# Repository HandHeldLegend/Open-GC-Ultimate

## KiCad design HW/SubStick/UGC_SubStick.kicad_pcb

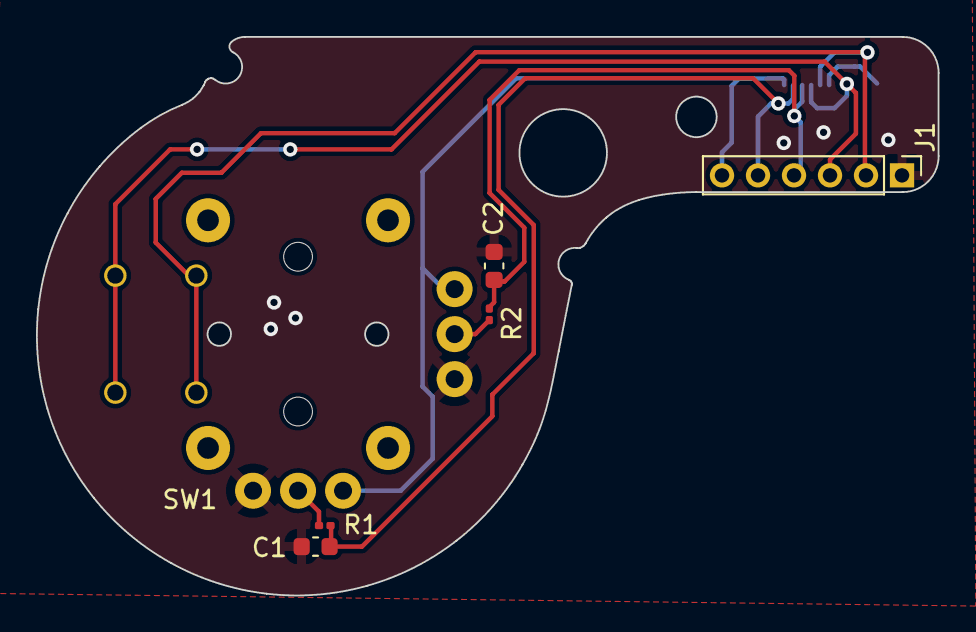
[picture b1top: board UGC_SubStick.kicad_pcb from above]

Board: 2 copper layers, 50.1 x 31.0 mm, 7 parts (1 on the bottom side), 8 nets.

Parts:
C1, C2: 47nF; C_0603_1608Metric
J1: Conn_01x06_Pin; PinHeader_1x06_P2.00mm_Vertical
J2: 503480-0640; 5034800640
R1, R2: 1k; R_0201_0603Metric
SW1: GL18_SW; GL1807SYAE

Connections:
+3V3: J1.6, J2.6, SW1.X3 (VCC), SW1.Y3 (VCC)
GND: C1.1, C2.1, J1.1, J2.1, J2.MP1, J2.MP2, SW1.X1 (GND), SW1.Y1 (GND)
unnamed: R1.1, SW1.X2 (X_OUT)
unnamed: R2.1, SW1.Y2 (Y_OUT)
RS_B_IN: J1.3, J2.3, SW1.S3 (3), SW1.S4 (4)
RS_B_OUT: J1.2, J2.2, SW1.S1 (1), SW1.S2 (2)
RX: C1.2, J1.5, J2.5, R1.2
RY: C2.2, J1.4, J2.4, R2.2

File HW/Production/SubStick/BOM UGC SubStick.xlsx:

NO | Designator | Quantity | Part Number（MPN) | Description | Value | Package | LCSC | Comment or Link | DNP
1.0 | SW1 | 1.0 | GL1807SYAE-002 | TMR Analog Stick with button | GL18_SW | - | - | -
2.0 | R1,R2 | 2.0 | RC0201FR-071KL | 50mW Thick Film Resistors 25V ±1% ±200ppm/℃ 1kΩ | 1k | 201.0 | C138165 | https://www.lcsc.com/product-detail/Chip-Resistor-Surface-Mo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
3.0 | C1,C2 | 2.0 | CC0603JRX7R9BB473 | 50V 47nF X7R ±5% | 47nF | 603.0 | C519554 | https://www.lcsc.com/product-detail/Multilayer-Ceramic-Capac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
4.0 | J2 | 1.0 | 5.03480064E9 | Connector FFC/FPC Connector Socket 6 Position 0.5mm Solder Right Angle Surface 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 | 503480-0640 | SMD,P=0.5mm,Surface Mount，Right Angle | C3168077 | https://www.lcsc.com/product-detail/FFC-FPC-Flat-Flexible-Co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

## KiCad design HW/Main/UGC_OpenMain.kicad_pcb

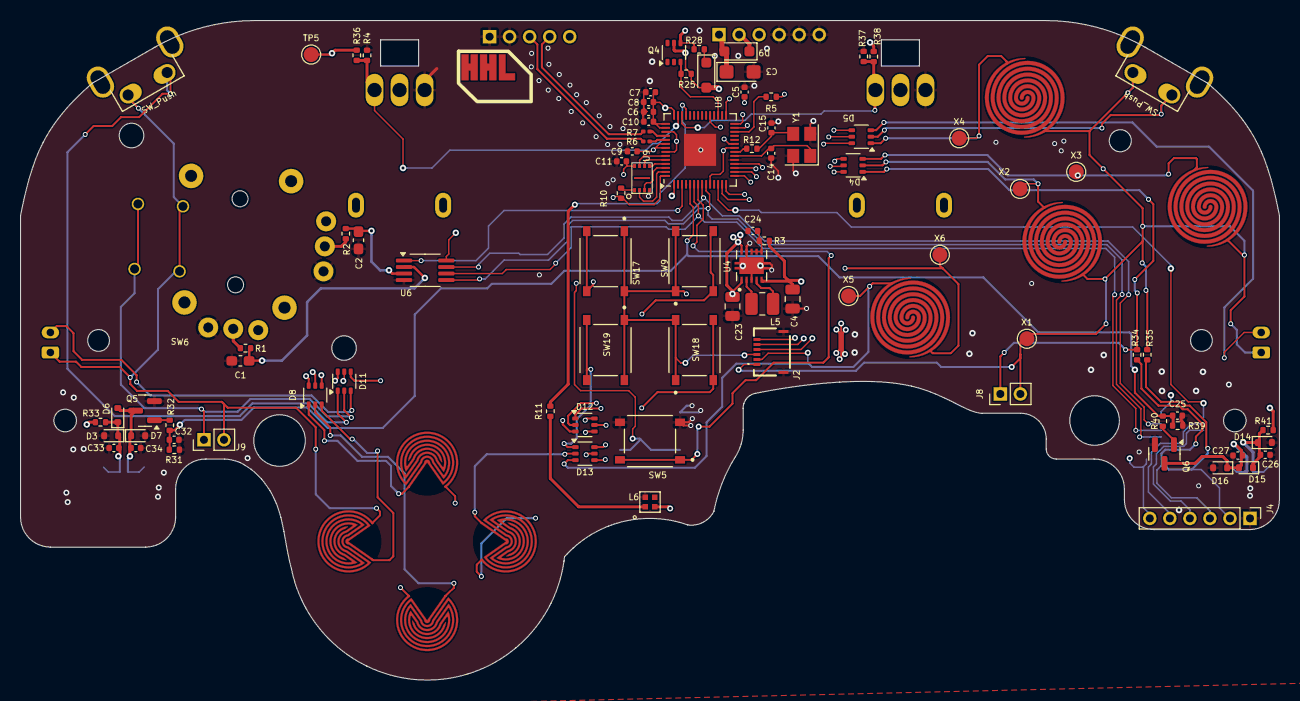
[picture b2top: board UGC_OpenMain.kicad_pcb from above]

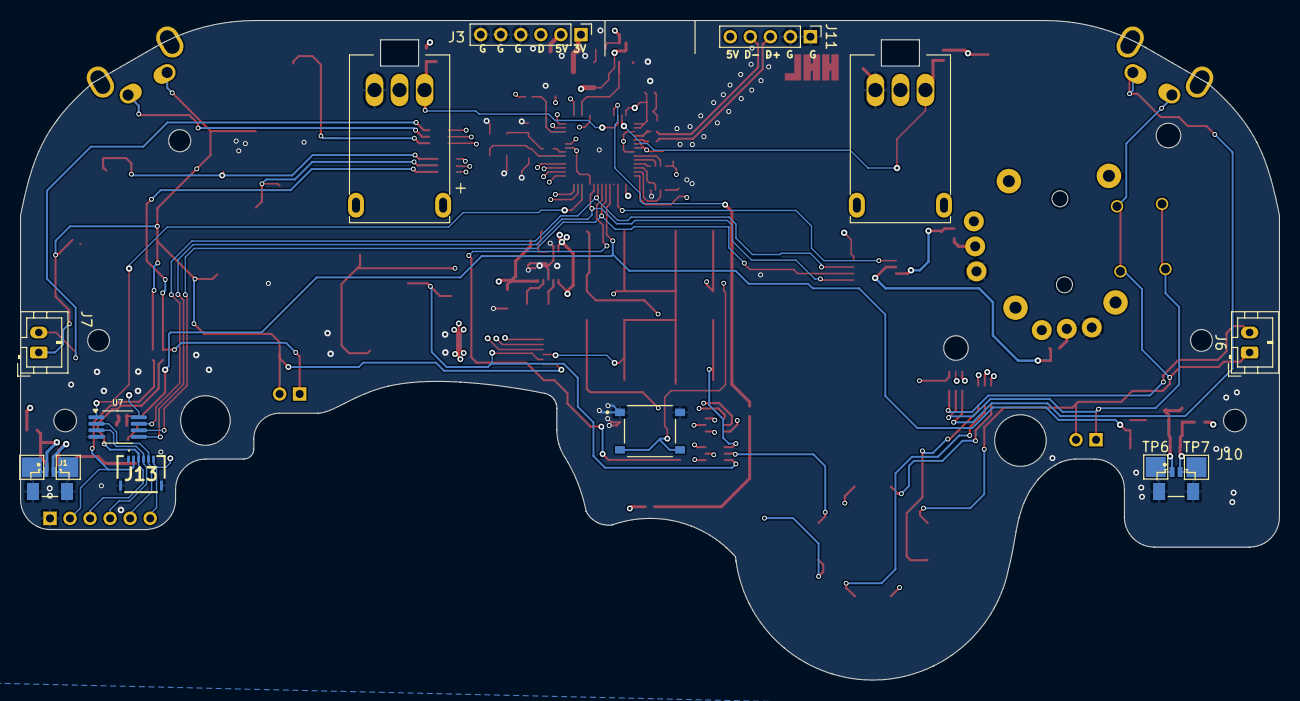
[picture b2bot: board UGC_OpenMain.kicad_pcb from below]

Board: 4 copper layers, 125.7 x 65.8 mm, 116 parts (21 on the bottom side), 78 nets.

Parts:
C1, C2: 47nF; C_0603_1608Metric_Pad1.08x0.95mm_HandSolder
C3: 47uF; CP_EIA-3216-18_Kemet-A
C4, C23: 10uF; C_0805_2012Metric
C5, C6, C7, C9, C10, C11, C24, C25, C32: 100nF; C_0402_1005Metric
C8, C26, C27, C33, C34: 1uF; C_0402_1005Metric
C14, C15: 15pF; C_0402_1005Metric
D3, D6, D7, D14, D15, D16: M7C; D_SOD-523
D4, D5, D8, D11, D12, D13: BAS16VY,115; SOT-363_SC-70-6
D9, D10: CUS08F30; D_SOD-323_HandSoldering
J1, J10: SM02B-SURS-TF_LF__SN_; JST_SM02B-SURS-TF_LF__SN_
J2, J13: 503480-0640; 5034800640
J3, J4: Conn_01x06_Pin; PinHeader_1x06_P2.00mm_Vertical
J6, J7: Trigger; JST_PH_B2B-PH-K_1x02_P2.00mm_Vertical
J8, J9: Conn_01x02; PinHeader_1x02_P2.00mm_Vertical
J11: Conn_01x05_Pin; PinHeader_1x05_P2.00mm_Vertical
L5: 1.3A 2.2uH ±20% 80mΩ; L_1008_2520Metric
L6: SK6805-EC-15
Q4: BSS138DW; SOT-363_SC-70-6
Q5, Q6: MMBT2222A; SOT-23
R1, R2, R10, R12, R25, R28: 1k; R_0402_1005Metric
R3, R32, R40: 100R; R_0402_1005Metric
R4, R36, R37, R38: 75k; R_0402_1005Metric
R5, R31, R39: 10k; R_0402_1005Metric
R6, R7: 27R; R_0201_0603Metric
R11: 330R; R_0402_1005Metric
R33, R34, R35, R41: 0R; R_0402_1005Metric
RV1, RV2: Slider_GCC-Gamecube_MB; GCC_Slider_MillMaxSocketed
S1, S2, S3, S4, S5, S6: 4015-0-43-80-30-27-10-0
SW1, SW2, SW3, SW4: SW_Push; ring_pad
SW5, SW9, SW14, SW17, SW18, SW19: SW_TS-1187A; TS-1187A-C-E-B
SW6: GL18_SW; GL1807SYAE
SW7, SW8: SW_Push; Z_Switch_Edge_Omron
SW10, SW11, SW12, SW13: SW_Push; ring_dpad
TP1, TP2, TP6, TP7: TestPoint; TestPoint_Pad_2.0x2.0mm
TP5: TestPoint; TestPoint_Pad_D1.5mm
U4: TPS630001RCR; VREG_V62_16624-01YE
U6, U7: MCP3002; MSOP-8_3x3mm_P0.65mm
U8: RP2040; QFN-56-1EP_7x7mm_P0.4mm_EP3.2x3.2mm
U9: GD25Q80EEIGR; USON-8-EP(2x3)
X1, X2, X3, X4, X5, X6: ModConnect; TestPoint_Pad_D1.5mm
Y1: ABM8-272-T3; Crystal_SMD_3225-4Pin_3.2x2.5mm

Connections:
+1V1: C5.2, U8.23 (DVDD), U8.45 (VREG_VOUT), U8.50 (DVDD)
+3V3: C6.1, C7.1, C8.1, C9.2, C10.2, C11.1, C23.1, D10.2 (A), J4.6, J13.6, L6.2 (VDD), Q4.5 (G2), R5.1, R25.1, R33.2, R36.2, R38.2, R41.2, S1.1, S4.1, SW6.X3 (VCC), SW6.Y3 (VCC), TP5.1, U4.1 (VOUT), U4.10 (FB), U6.8 (VDD/VREF), U7.8 (VDD/VREF), U8.1 (IOVDD), U8.10 (IOVDD), U8.22 (IOVDD), U8.33 (IOVDD), U8.42 (IOVDD), U8.43 (ADC_AVDD), U8.44 (VREG_IN), U8.48 (USB_VDD), U8.49 (IOVDD), U9.8 (VCC)
+3V3_PRE: C3.1, D9.2 (A), J3.1
A: D4.6 (K), D8.6 (K), D12.6 (K), U8.29 (GPIO18)
B: D4.5 (K), D8.5 (K), D12.5 (K), U8.28 (GPIO17)
BTN_PWR: SW5.A, SW5.B, U8.7 (GPIO5)
C: D4.4 (K), D8.4 (K), D12.4 (K), U8.27 (GPIO16)
D: D5.6 (K), D11.6 (K), D13.6 (K), U8.18 (GPIO15)
D+: J11.3, R6.1
D-: J11.4, R7.1
E: D5.5 (K), D11.5 (K), D13.5 (K), U8.17 (GPIO14)
F: D5.4 (K), D11.4 (K), D13.4 (K), U8.16 (GPIO13)
G: J2.1, J7.1, J8.2, R35.2, SW1.1, SW3.1, SW4.1, SW8.1, U8.15 (GPIO12), X1.1
GND: C1.1, C2.1, C3.2, C4.1, C5.1, C6.2, C7.2, C8.2, C9.1, C10.1, C11.2, C14.2, C15.2, C23.2, C24.1, C25.2, C26.1, C27.2, C32.2, C33.1, C34.2, D3.2 (A), D7.2 (A), D14.2 (A), D16.2 (A), J1.S1 (SHIELD), J1.S2 (SHIELD), J2.MP1, J2.MP2, J3.4, J3.5, J3.6, J4.1, J10.S1 (SHIELD), J10.S2 (SHIELD), J11.1, J11.2, J13.1, J13.MP1, J13.MP2, L6.4 (GND), Q5.2 (E), Q6.2 (E), R4.1, R31.1, R37.1, R39.1, S3.1, S6.1, SW5.C, SW5.D, SW6.X1 (GND), SW6.Y1 (GND), SW14.A, SW14.B, U4.3 (PGND), U4.9 (GND), U4.11 (EP), U6.4 (VSS), U7.4 (VSS), U8.19 (TESTEN), U8.57 (GND), U9.4 (VSS), Y1.2, Y1.4
H: J6.1, J9.2, SW6.S1 (1), SW6.S2 (2), SW7.1, SW10.1, SW11.1, SW12.1, U8.14 (GPIO11)
I: J2.3, SW2.1, SW9.A, SW9.B, SW13.1, SW17.A, SW17.B, SW18.A, SW18.B, SW19.A, SW19.B, U8.13 (GPIO10), X6.1
LADC_CS: U6.1 (~CS/SHDN), U8.3 (GPIO1)
LRA_L+: C33.2, D3.1 (K), D6.1 (K), J10.2, R33.1, TP7.1
LRA_L-: C34.1, D6.2 (A), D7.1 (K), J10.1, Q5.3 (C), TP6.1
LRA_R+: C26.2, D14.1 (K), D15.1 (K), J1.1, R41.1, TP2.1
LRA_R-: C27.1, D15.2 (A), D16.1 (K), J1.2, Q6.3 (C), TP1.1
LS_BTN_IN: D11.2 (A), J9.1, SW6.S3 (3), SW6.S4 (4)
LX: C1.2, R1.2, U6.2 (CH0)
LY: C2.2, R2.2, U6.3 (CH1)
N_DATA: J3.3, Q4.4 (S2), R28.2
N_DATA_3.3: Q4.3 (D2), R25.2, U8.31 (GPIO20)
unnamed: C15.1, R12.2, Y1.3
unnamed: D4.1 (A), J8.1, R34.1
unnamed: D5.2 (A), SW8.2
unnamed: D5.3 (A), J7.2
unnamed: D8.1 (A), SW10.2
unnamed: D8.2 (A), SW11.2
unnamed: D8.3 (A), SW12.2
unnamed: D11.1 (A), SW7.2
unnamed: D11.3 (A), J6.2
unnamed: D12.1 (A), SW9.C, SW9.D
unnamed: D12.2 (A), SW17.C, SW17.D
unnamed: D12.3 (A), SW18.C, SW18.D
unnamed: D13.1 (A), SW19.C, SW19.D
unnamed: D13.2 (A), SW13.2
unnamed: Q5.1 (B), R32.2
unnamed: Q6.1 (B), R40.2
unnamed: R1.1, SW6.X2 (X_OUT)
unnamed: R2.1, SW6.Y2 (Y_OUT)
unnamed: C24.2, R3.2, U4.6 (EN), U4.7 (PS/SYNC), U4.8 (VINA)
unnamed: L5.1, U4.4 (L1)
unnamed: L5.2, U4.2 (L2)
unnamed: R7.2, U8.46 (USB_DM)
unnamed: R6.2, U8.47 (USB_DP)
unnamed: R10.2, U9.1 (/CS)
RADC_CS: U7.1 (~CS/SHDN), U8.12 (GPIO9)
RGB_OUT: R11.2, U8.39 (GPIO27_ADC1)
RP_RUN: R5.2, U8.26 (RUN)
RS_B_IN: J4.2, J13.2, R35.1
RS_B_OUT: J4.3, J13.3, R34.2
RUMBLE_OUT: C25.1, C32.1, R31.2, R32.1, R39.2, R40.1, U8.5 (GPIO3)
RX: J4.5, J13.5, U7.2 (CH0)
RY: J4.4, J13.4, U7.3 (CH1)
SCLK: U8.52 (QSPI_SCLK), U9.6 (SCLK)
SHARED_PU: D10.1 (K), R28.1
SIO0: U8.53 (QSPI_SD0), U9.5 (IO0)
SIO1: U8.55 (QSPI_SD1), U9.2 (IO1)
SIO2: U8.54 (QSPI_SD2), U9.3 (IO2)
SIO3: U8.51 (QSPI_SD3), U9.7 (IO3)
SL_RGB: L6.1 (DIN), R11.1
SPI_CK: U6.7 (CLK), U7.7 (CLK), U8.8 (GPIO6)
SPI_RX: U6.6 (DOUT), U7.6 (DOUT), U8.6 (GPIO4)
SPI_TX: U6.5 (DIN), U7.5 (DIN), U8.9 (GPIO7)
USB_BOOT: R10.1, SW14.C, SW14.D, U8.56 (QSPI_SS)
VBUS_SYS: C4.2, D9.1 (K), J3.2, J11.5, R3.1, U4.5 (VIN)
X2: D4.2 (A), J2.4, SW1.2, X2.1
X3: D4.3 (A), J2.5, SW3.2, X3.1
X4: D5.1 (A), J2.6, SW4.2, X4.1
X5: D13.3 (A), J2.2, SW2.2, X5.1
XTAL_IN: C14.1, U8.20 (XIN), Y1.1
XTAL_OUT: R12.1, U8.21 (XOUT)
ZL_ANALOG: R4.2, R36.1, S2.1, U8.41 (GPIO29_ADC3)
ZR_ANALOG: R37.2, R38.1, S5.1, U8.40 (GPIO28_ADC2)

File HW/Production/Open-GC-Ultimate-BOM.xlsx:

Reference | Value | MPN | Price | LCSC | Footprint | Qty | DNP | Notes
C1,C2 | 47nF | CC0603JRX7R9BB473 | 0.0026 | C519554 | Capacitor_SMD:C_0603_1608Metric_Pad1.08x0.95mm_HandSolder | 2.0
C3 | 47uF | TAJA476K006RNJ | 0.0544 | C7190 | Capacitor_Tantalum_SMD:CP_EIA-3216-18_Kemet-A | 1.0
C4,C23 | 10uF | CL21A106KPFNNNE | 0.005 | C17024 | Capacitor_SMD:C_0805_2012Metric | 2.0
C5,C6,C7,C9,C10,C11,C24,C25,C32 | 100nF | CC0402KRX7R5BB104 | 7.0E-4 | C541406 | Capacitor_SMD:C_0402_1005Metric | 9.0
C8,C26,C27,C33,C34 | 1uF | CL05A105KQ5NNNC | 9.0E-4 | C107372 | Capacitor_SMD:C_0402_1005Metric | 5.0
C14,C15 | 15pF | CC0402FRNPO9BN150 | 0.0022 | C326803 | Capacitor_SMD:C_0402_1005Metric | 2.0
D3,D6,D7,D14,D15,D16 | M7C | B5819WT | 0.0179 | C5364321 | Diode_SMD:D_SOD-523 | 6.0
D4,D5,D8,D11,D12,D13 | BAS16VY,115 | BAS16VY,115 | 0.0186 | C135826 | Package_TO_SOT_SMD:SOT-363_SC-70-6 | 6.0
D9,D10 | CUS08F30 | CUS08F30 | 0.0092 | C27636112 | Diode_SMD:D_SOD-323_HandSoldering | 2.0
J1,J10 | SM02B-SURS-TF_LF__SN_ | SM02B-SURS-TF(LF)(SN) | 0.108 | C566239 | hhl:JST_SM02B-SURS-TF_LF__SN_ | 2.0
J2,J13 | 503480-0640 | 503480-0640 | 0.4028 | C3168077 | hhl:5034800640 | 2.0
J3 | Conn_01x06_Pin | N/A |  |  | Connector_PinHeader_2.00mm:PinHeader_1x06_P2.00mm_Vertical | 1.0 | DNP
J6,J7 | Trigger | PH2.0 mm Female | 0.0098 | C7499302 | Connector_JST:JST_PH_B2B-PH-K_1x02_P2.00mm_Vertical | 2.0
J11 | Conn_01x05_Pin | ZX-PZ2.0-1-5PZZ | 0.019 | C7501286 | Connector_PinHeader_2.00mm:PinHeader_1x05_P2.00mm_Vertical | 1.0 |  | USB Breakout
L5 | 1.3A 2.2uH ±20% 80mΩ | MIP25202R2MBE | 0.0208 | C315721 | Inductor_SMD:L_1008_2520Metric | 1.0
L6 | SK6805-EC-15 | SK6805-EC-15 | 0.0492 | C2890035 | hhl:SK6805-EC-15 | 1.0
Q4 | BSS138DW | BSS138DW-7-F | 0.037 | C154900 | Package_TO_SOT_SMD:SOT-363_SC-70-6 | 1.0
Q5,Q6 | MMBT2222A | MMBT2222A | 0.005 | C916372 | Package_TO_SOT_SMD:SOT-23 | 2.0
R1,R2,R10,R12,R25,R28 | 1k | RC0402FR-071KL | 4.0E-4 | C106235 | Resistor_SMD:R_0402_1005Metric | 6.0
R3,R32,R40 | 100R | RC0402FR-07100RL | 5.0E-4 | C106232 | Resistor_SMD:R_0402_1005Metric | 3.0
R4,R36,R37,R38 | 75k | RC0402FR-0775KL | 4.0E-4 | C137935 | Resistor_SMD:R_0402_1005Metric | 4.0
R5,R31,R39 | 10k | RC0402FR-0710KL | 4.0E-4 | C60490 | Resistor_SMD:R_0402_1005Metric | 3.0
R6,R7 | 27R | RC0201FR-0727RL | 6.0E-4 | C273268 | Resistor_SMD:R_0201_0603Metric | 2.0
R11 | 330R | RC0402FR-07330RL | 5.0E-4 | C105875 | Resistor_SMD:R_0402_1005Metric | 1.0
R33,R34,R35,R41 | 0R | RC0402FR-070RL | 4.0E-4 | C106231 | Resistor_SMD:R_0402_1005Metric | 4.0
RV1,RV2 | Slider_GCC-Gamecube_MB | RD7091008A | 0.2624 | C127475 | hhl:GCC_Slider_MillMaxSocketed | 2.0
S1,S2,S3,S4,S5,S6 | 4015-0-43-80-30-27-10-0 | 4015-0-43-80-30-27-10-0 | 0.754 | C17526581 | hhl:4015-0-43-80-30-27-10-0 | 6.0
SW5,SW9,SW14,SW17,SW18,SW19 | SW_TS-1187A | TS-1187A-C-E-B | 0.0197 | C318887 | hhl:TS-1187A-C-E-B | 6.0
SW6 | GL18_SW | GL1807SYAE-002 | 1.9 |  | hhl:GL1807SYAE | 1.0 |  | Supplied by GuliKit
SW7,SW8 | SW_Push | TC-00100V H5.0 100gf | 0.082 |  | hhl:Z_Switch_Edge_Omron | 2.0 |  | Must be supplied externally
U4 | TPS630001RCR | TPS63001DRCR | 0.565 | C28060 | hhl:VREG_V62_16624-01YE | 1.0
U6,U7 | MCP3002 | MCP3002-I/MS | 1.11 | C635958 | Package_SO:MSOP-8_3x3mm_P0.65mm | 2.0
U8 | RP2040 | RP2040 | 0.531 | C2040 | Package_DFN_QFN:QFN-56-1EP_7x7mm_P0.4mm_EP3.2x3.2mm | 1.0
U9 | GD25Q80EEIGR | GD25Q80EEIGR | 0.22 | C2874937 | hhl:USON-8-EP(2x3) | 1.0
Y1 | ABM8-272-T3 | ABM8-272-T3 | 0.2381 | C20625731 | Crystal:Crystal_SMD_3225-4Pin_3.2x2.5mm | 1.0

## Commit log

2024-10-29 Commit PCB Files
2024-10-29 Update ignore
2024-10-29 Add accessory boards
2024-10-29 Add cable plug
2024-10-29 Update all BOM etc.
2024-10-29 Remove backups
2024-10-29 Update accessories
2025-02-02 Move FW
